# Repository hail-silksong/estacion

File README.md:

# estacion
estacion metereologica infantil
POR SUPUESTO XD

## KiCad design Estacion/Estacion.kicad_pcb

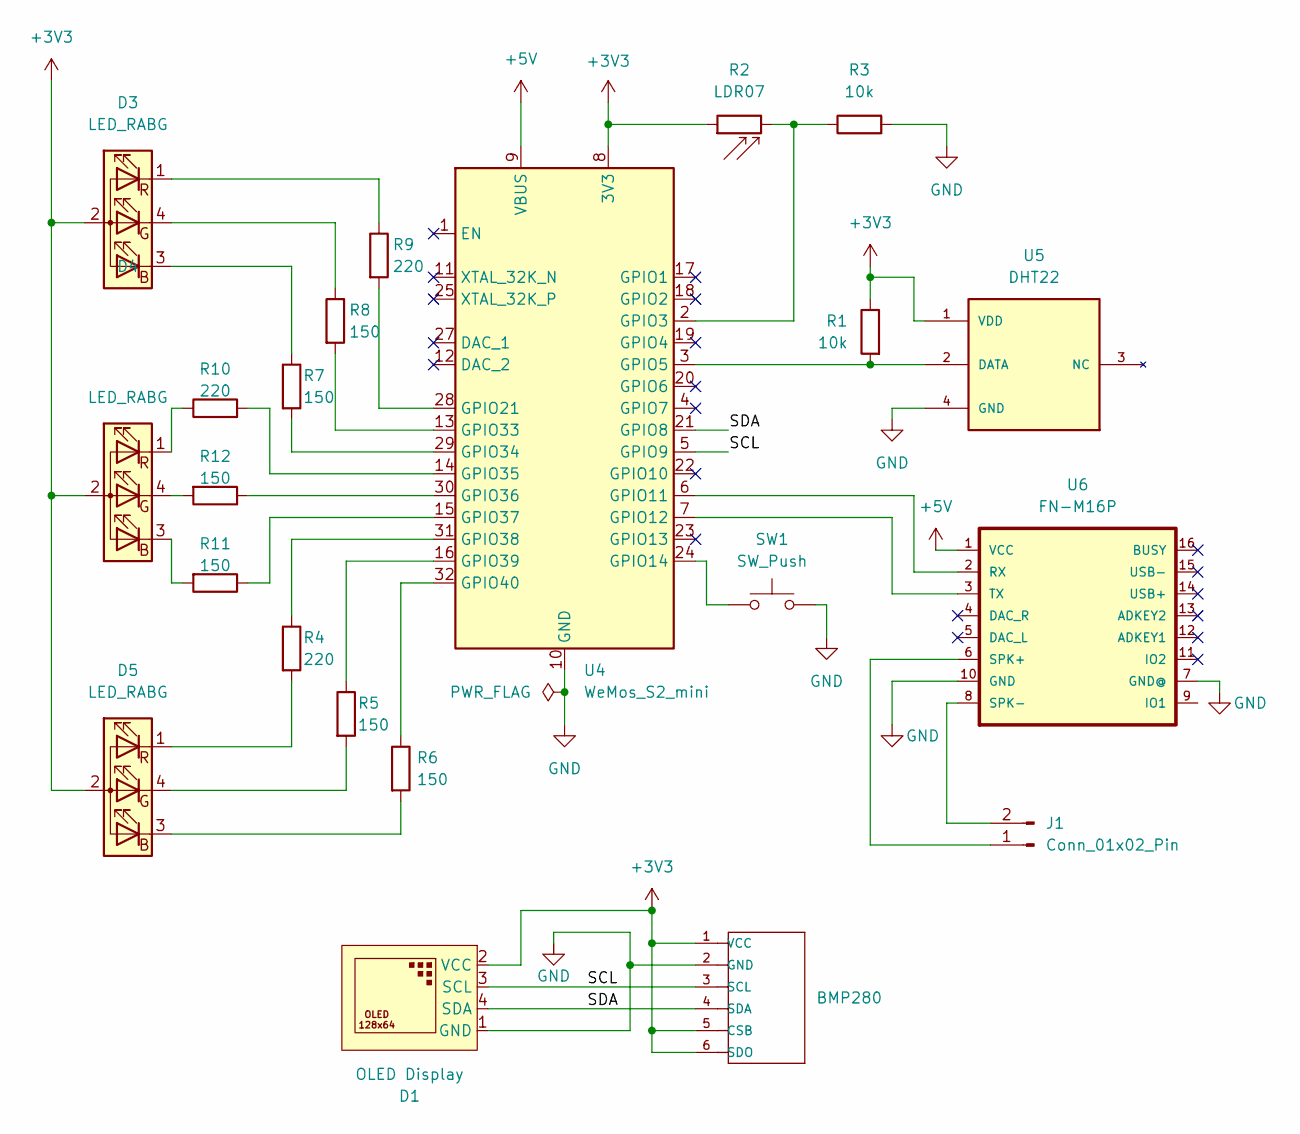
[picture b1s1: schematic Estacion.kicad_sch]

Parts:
BMP280: BMP18; BMP180; MPN BMP18
D1: OLED Display; OLED-Display_SSD1306_128x64
D3, D4, D5: LED_RABG; LED_D5.0mm-4_RGB_Wide_Pins
J1: Conn_01x02_Pin; PinHeader_1x02_P2.54mm_Vertical
R1, R3: 10k; R_1206_3216Metric_Pad1.30x1.75mm_HandSolder
R2: LDR07; R_LDR_5.1x4.3mm_P3.4mm_Vertical
R4, R9, R10: 220; R_0805_2012Metric_Pad1.20x1.40mm_HandSolder
R5, R6, R7, R8, R11, R12: 150; R_0805_2012Metric_Pad1.20x1.40mm_HandSolder
SW1: SW_Push; SW_PUSH_6mm
U4: WeMos_S2_mini; WEMOS_S2_mini
U5: DHT22; XDCR_DHT22
U6: FN-M16P

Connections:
+3V3: BMP280.1 (VCC), BMP280.5 (CSB), BMP280.6 (SDO), D1.2 (VCC), D3.2 (A), D4.2 (A), D5.2 (A), R1.1, R2.1, U4.8 (3V3), U5.1 (VDD)
+5V: U4.9 (VBUS), U6.1 (VCC)
/SCL: BMP280.3 (SCL), D1.3 (SCL), U4.5 (GPIO9)
/SDA: BMP280.4 (SDA), D1.4 (SDA), U4.21 (GPIO8)
GND: BMP280.2 (GND), D1.1 (GND), R3.2, SW1.1, U4.10 (GND), U4.26 (GND), U5.4 (GND), U6.7 (GND@), U6.10 (GND)
unnamed: D3.3 (BK), R7.1
unnamed: D3.4 (GK), R8.1
unnamed: D3.1 (RK), R9.1
unnamed: D4.3 (BK), R11.2
unnamed: D4.4 (GK), R12.2
unnamed: D4.1 (RK), R10.1
unnamed: D5.3 (BK), R6.2
unnamed: D5.4 (GK), R5.2
unnamed: D5.1 (RK), R4.2
unnamed: J1.1, U6.6 (SPK+)
unnamed: J1.2, U6.8 (SPK-)
unnamed: R2.2, R3.1, U4.2 (GPIO3)
unnamed: R1.2, U4.3 (GPIO5), U5.2 (DATA)
unnamed: U4.6 (GPIO11), U6.2 (RX)
unnamed: U4.7 (GPIO12), U6.3 (TX)
unnamed: SW1.2, U4.24 (GPIO14)
unnamed: R9.2, U4.28 (GPIO21)
unnamed: R8.2, U4.13 (GPIO33)
unnamed: R7.2, U4.29 (GPIO34)
unnamed: R10.2, U4.14 (GPIO35)
unnamed: R12.1, U4.30 (GPIO36)
unnamed: R11.1, U4.15 (GPIO37)
unnamed: R4.1, U4.31 (GPIO38)
unnamed: R5.1, U4.16 (GPIO39)
unnamed: R6.1, U4.32 (GPIO40)

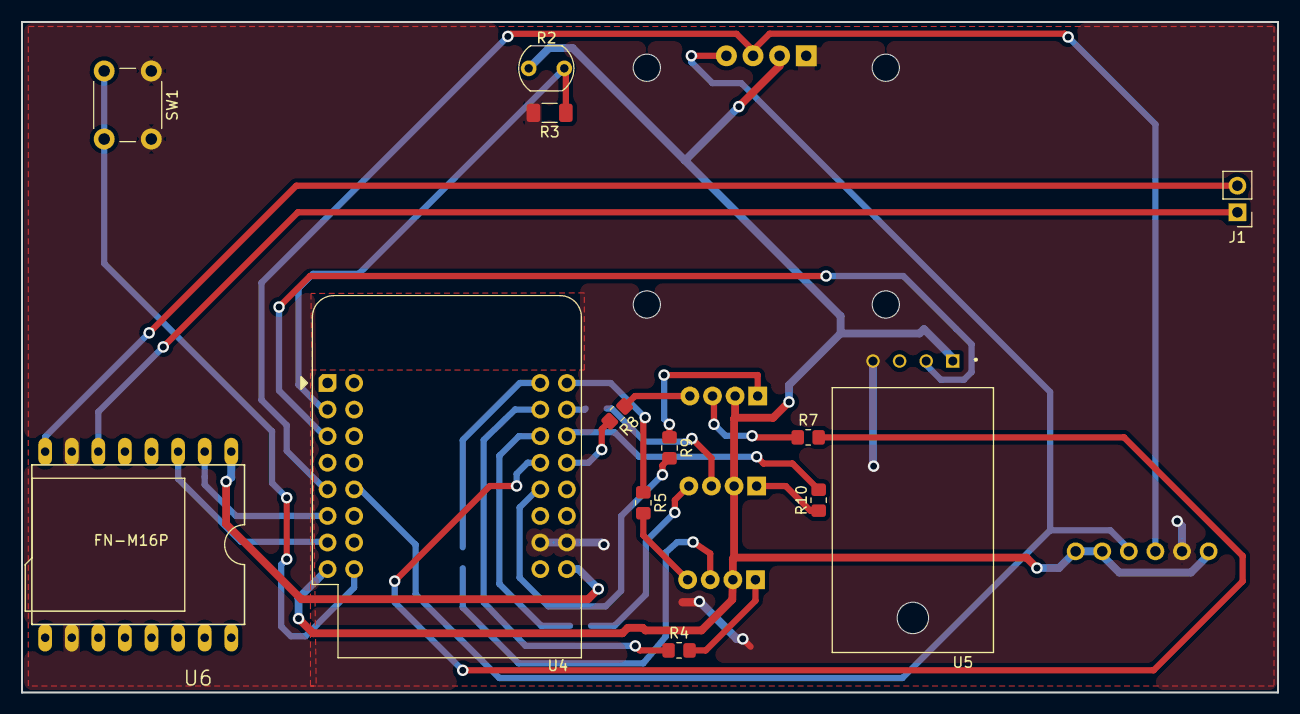
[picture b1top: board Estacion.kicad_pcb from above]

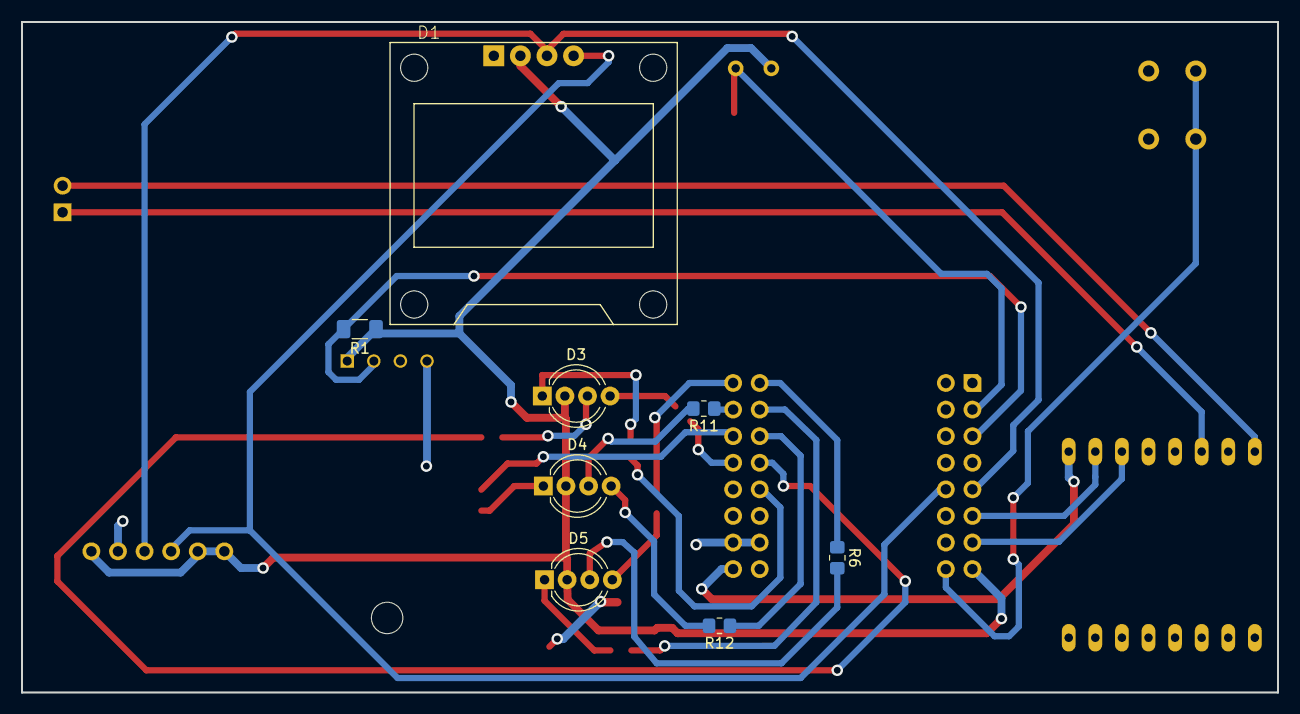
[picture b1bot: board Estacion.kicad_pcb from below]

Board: 2 copper layers, 120.0 x 64.1 mm, 22 parts (8 on the bottom side), 30 nets.

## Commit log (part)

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2026-06-23 PRUEBA github
2026-06-23 Importaciones
    Todos los simbolos y huellas que no estan por defecto en el kicad
2026-06-23 Asociar simbolos con huellas
2026-06-24 preparaciones
    Relacionar footprints con modelados 3d, delimitar espacio de pcb, retocar conexiones y asegurar cumplimiento de ERC
2026-06-24 descarte archivos innecesarios
2026-06-24 Wemos s2 mini
    Se cambia el controlador y se realizan las conexiones en el diagrama
2026-06-24 Girar los GND para que apunten abajo y agregar la net 3v3
